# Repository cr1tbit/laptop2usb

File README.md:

# laptop2usb

### The premises
 
  * In tech-oriented public spaces there's constant shortage of wallplug USB chargers
  * The notebooks' powerbricks generally outlive the notebooks themself, so with enough effort you may get one for free
 
### How do I?

You fasten the PCB to a powerbrick.

The device takes anything between 17-20V, converts it into 5V, and splits into multiple USB and screw terminal ports. All of these ports are polyfuse-protected.

### Status

I'm yet to check a couple of things, and will do rev.2:
  * The converter gets super hot right now - is this OK? Calculate and document thermal resistance stuff. Verify converter efficiency.
  * Is the 10 mOhm current-limiting resistor even working?
  * The future is now - add USB C?
  * Maximum current it can handle (it was designed for 8A max, but I doubt it'll survive that for long)
  * Are USB ports wired properly? Do android/iOS/raspberry PIs utilize it well enough?
  * Now check the first letters of the list

### Trivia

I ordered the prototype from JLCPcb, with passive elements surface mounted. Their online tool automatically assigns the elements from BOM into the part numbers from their store. Apparently it parsed the shunt 10mOhm resistor as 10 Mega Ohms. 

With 10MegaOhms in the power path, the LM25085 somehow managed to produce 4V output with enough current to shine an onboard LED. Now that's dedication.

EDIT: it's been 2 years and one of my friends at work did literally the same kind of mistake when ordering PCBA from circuithub. I managed to catch that mistake quite fast, and implement a fix. I guess the lesson is, that those silly side-projects are really not in vain.

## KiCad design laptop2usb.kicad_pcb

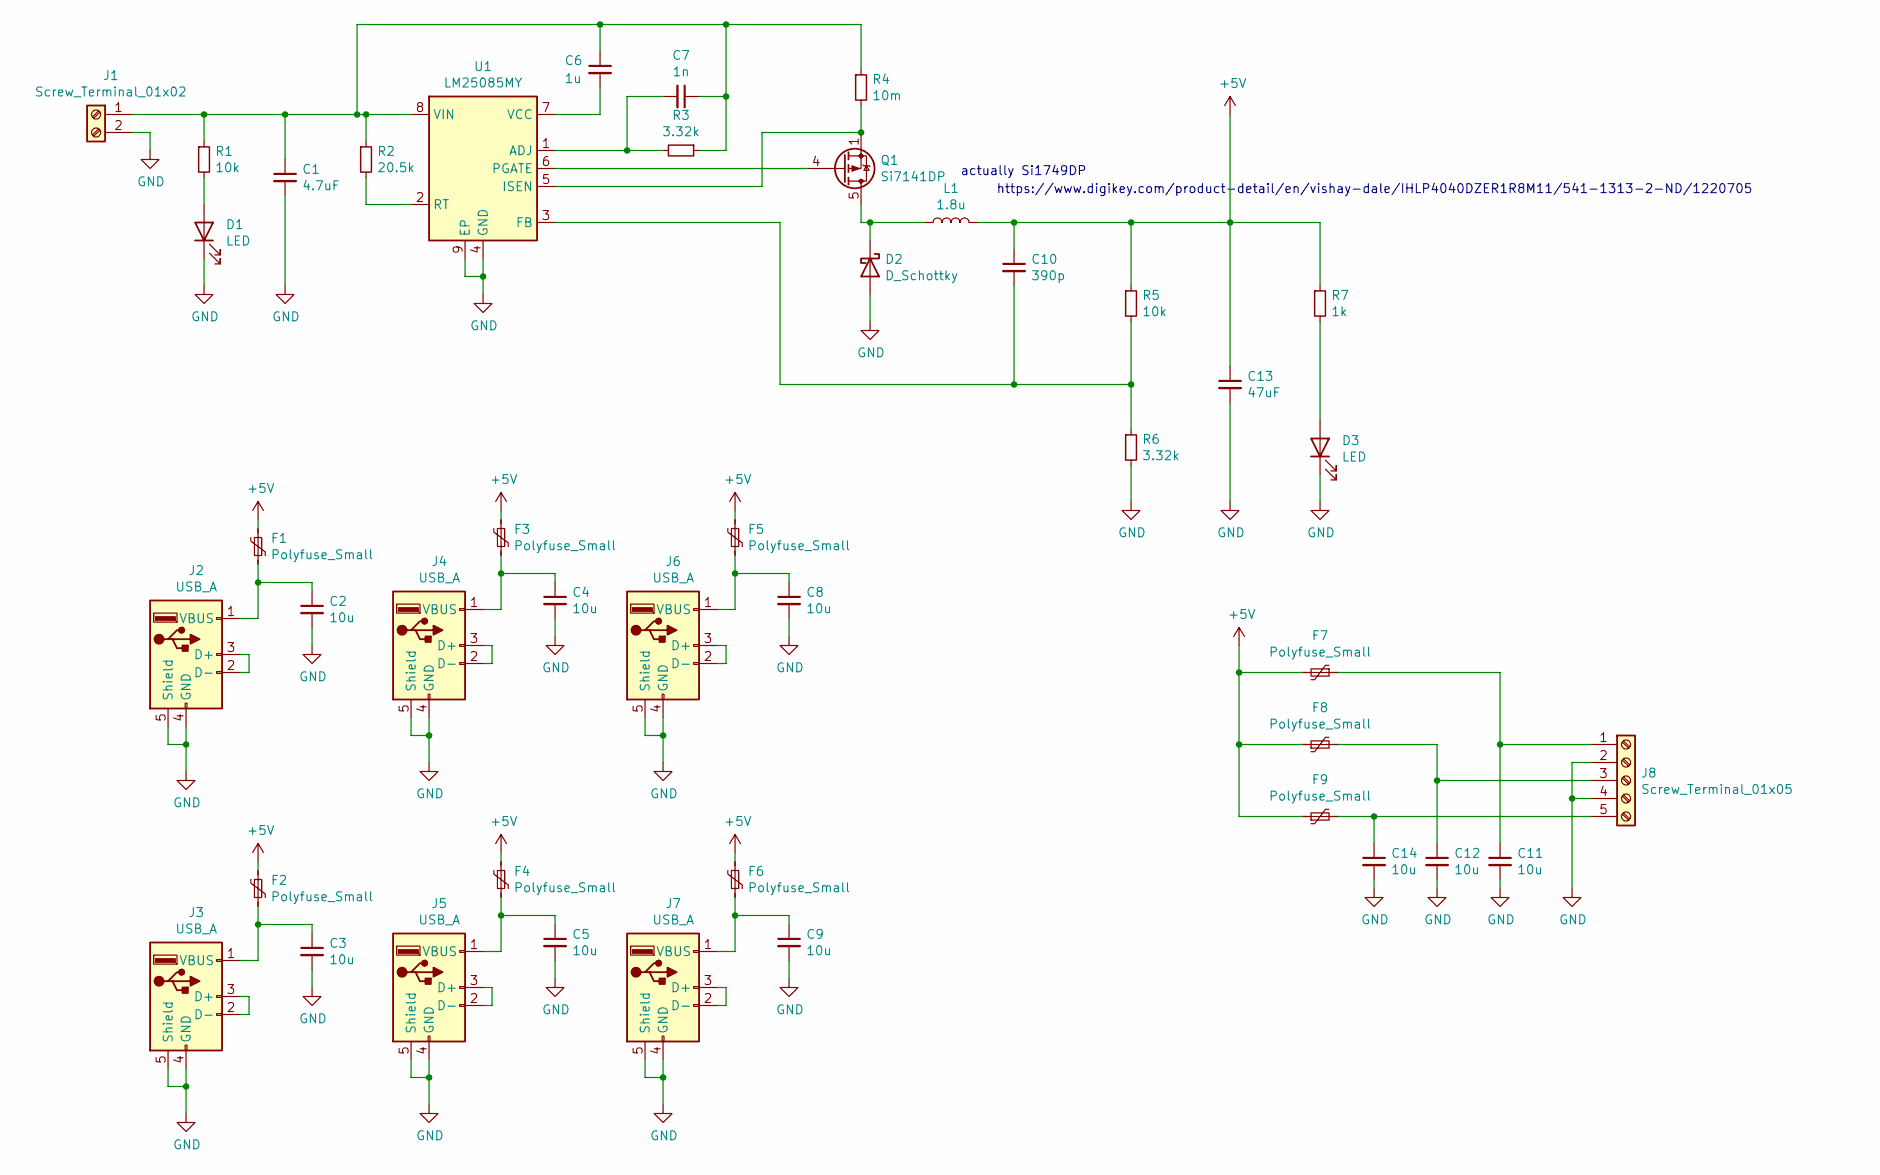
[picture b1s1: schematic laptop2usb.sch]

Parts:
C1: 4.7uF; C_0603_1608Metric_Pad1.05x0.95mm_HandSolder
C2, C3, C4, C5, C8, C9, C11, C12, C14: 10u; C_0603_1608Metric_Pad1.05x0.95mm_HandSolder
C6: 1u; C_0603_1608Metric_Pad1.05x0.95mm_HandSolder
C7: 1n; C_0603_1608Metric_Pad1.05x0.95mm_HandSolder
C10: 390p; C_0603_1608Metric_Pad1.05x0.95mm_HandSolder
C13: 47uF; C_1210_3225Metric_Pad1.42x2.65mm_HandSolder
D1, D3: LED; LED_1206_3216Metric_Pad1.42x1.75mm_HandSolder
D2: D_Schottky; D_SMB_Handsoldering
F1, F2, F3, F4, F5, F6, F7, F8, F9: Polyfuse_Small; Fuse_2920_7451Metric_Pad2.10x5.45mm_HandSolder
J1: Screw_Terminal_01x02; TerminalBlock_bornier-2_P5.08mm
J2, J3, J4, J5, J6, J7: USB_A; USB_A_Molex_67643_Horizontal
J8: Screw_Terminal_01x05; TerminalBlock_bornier-5_P5.08mm
L1: 1.8u; L_Vishay_IHLP-4040
Q1: Si7141DP; PowerPAK_SO-8_Single
R1, R5: 10k; R_0603_1608Metric_Pad1.05x0.95mm_HandSolder
R2: 20.5k; R_0603_1608Metric_Pad1.05x0.95mm_HandSolder
R3, R6: 3.32k; R_0603_1608Metric_Pad1.05x0.95mm_HandSolder
R4: 10m; R_0805_2012Metric_Pad1.15x1.40mm_HandSolder
R7: 1k; R_0603_1608Metric_Pad1.05x0.95mm_HandSolder
U1: LM25085MY; MSOP-8-1EP_3x3mm_P0.65mm_EP1.73x1.85mm_ThermalVias

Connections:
+5V: C10.1, C13.1, F1.1, F2.1, F3.1, F4.1, F5.1, F6.1, F7.2, F8.1, F9.1, L1.1, R5.1, R7.1
GND: C1.2, C2.2, C3.2, C4.2, C5.2, C8.2, C9.2, C11.2, C12.2, C13.2, C14.2, D1.1 (K), D2.2 (A), D3.1 (K), J1.2, J2.4 (GND), J2.5 (Shield), J3.4 (GND), J3.5 (Shield), J4.4 (GND), J4.5 (Shield), J5.4 (GND), J5.5 (Shield), J6.4 (GND), J6.5 (Shield), J7.4 (GND), J7.5 (Shield), J8.2, J8.4, R6.2, U1.4 (GND), U1.9 (EP)
unnamed: C1.1, C6.1, C7.1, J1.1, R1.1, R2.1, R3.1, R4.1, U1.8 (VIN)
unnamed: C2.1, F1.2, J2.1 (VBUS)
unnamed: C3.1, F2.2, J3.1 (VBUS)
unnamed: C4.1, F3.2, J4.1 (VBUS)
unnamed: C5.1, F4.2, J5.1 (VBUS)
unnamed: C6.2, U1.7 (VCC)
unnamed: C7.2, R3.2, U1.1 (ADJ)
unnamed: C8.1, F5.2, J6.1 (VBUS)
unnamed: C9.1, F6.2, J7.1 (VBUS)
unnamed: C10.2, R5.2, R6.1, U1.3 (FB)
unnamed: C11.1, F7.1, J8.1
unnamed: C12.1, F8.2, J8.3
unnamed: C14.1, F9.2, J8.5
unnamed: D1.2 (A), R1.2
unnamed: D2.1 (K), L1.2, Q1.5 (D)
unnamed: D3.2 (A), R7.2
unnamed: J2.2 (D-), J2.3 (D+)
unnamed: J3.2 (D-), J3.3 (D+)
unnamed: J4.2 (D-), J4.3 (D+)
unnamed: J5.2 (D-), J5.3 (D+)
unnamed: J6.2 (D-), J6.3 (D+)
unnamed: J7.2 (D-), J7.3 (D+)
unnamed: Q1.1 (S), Q1.2 (S), Q1.3 (S), R4.2, U1.5 (ISEN)
unnamed: Q1.4 (G), U1.6 (PGATE)
unnamed: R2.2, U1.2 (RT)

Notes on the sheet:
actually Si1749DP
https://www.digikey.com/product-detail/en/vishay-dale/IHLP4040DZER1R8M11/541-1313-2-ND/1220705

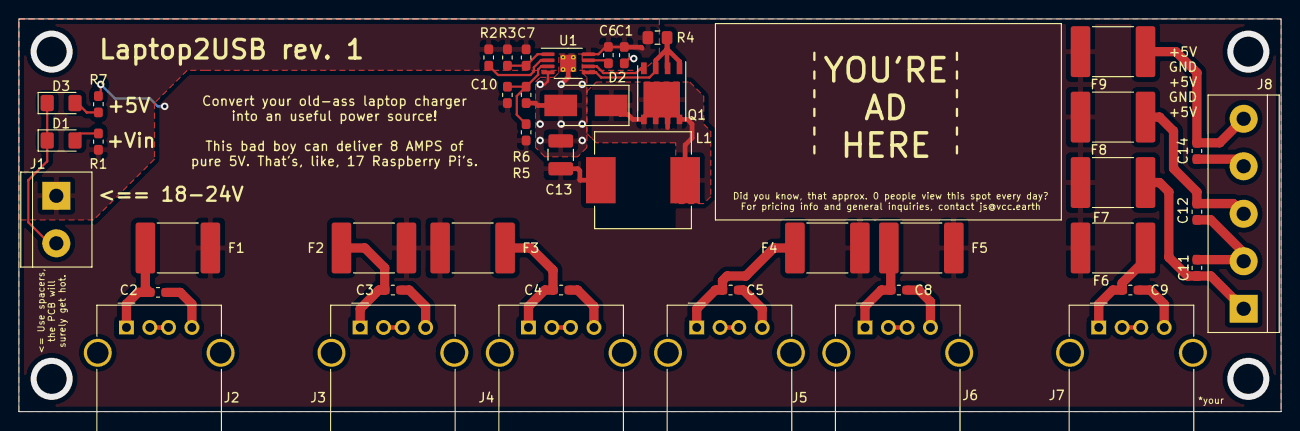
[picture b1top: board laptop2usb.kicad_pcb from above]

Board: 2 copper layers, 135.0 x 42.0 mm, 44 parts (0 on the bottom side), 27 nets.

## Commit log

2020-08-08 gityfying project
2020-08-08 Scrabble word finder
2020-08-08 adding images
2020-08-08 Fixing stuff in readme
